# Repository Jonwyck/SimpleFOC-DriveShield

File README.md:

> Fork additions: [v1.8 pinout and jumper guide](Design/DriveShield_pinout.org), [HTML guide](Design/DriveShield_pinout.html), and [initial KiCad 10 import](KiCad/README.org). The KiCad copy needs ERC/DRC and library/linkage cleanup before fabrication. Original EasyEDA design files remain unchanged.

# *Simple**FOC*** ***Drive**Shield* *v1.8*

This is an open-source low-cost BLDC driver boards in the form of a Arduino shield. It is a part of the *Simple**FOC*** project. The board is the big brother of the *Simple**FOC**Shield* and is designed to drive motors with higher current requirements, up to 40Amps. The board is created with the same philosophy as the *Simple**FOC**Shield* - to be simple to use, low-cost, and open-source and fully compatible with the *Simple**FOC***library. 

Additionally the aim of the board is to serve as a template project for the community to build their own motor drivers. 
- The board is relatively simple and can be easily modified to fit different requirements.
- The board is designed in EasyEDA and all the fabrication files are available for download

📢 NEW: This board is now available in our collaboration with **Makerfabs**: [See more on makerfabs.com](https://www.makerfabs.com/simplefoc-driveshield.html)

### Components
- **DRV8320H** gate driver - [datahseet](https://www.ti.com/lit/ds/symlink/drv8320.pdf?ts=178671431434)
   - Hardware configuration 
   - 3PWM 
   - Protections: undervoltage lockout, charge pump fault, MOSFET overcurrent, MOSFET short circuit, gate driver fault and overtemperature
- **BSZ0904NSI** mosfets
   - Standard 3mm x 3mm footprint (can be easily exchanged)
   - Max current 75A 
   - Max voltage 30V
- **INA240A1**: - [datasheet](https://www.ti.com/lit/ds/symlink/ina240.pdf?ts=1786684614540)
   - Inline current sensor
   - Gain 20V/V
   - Shunt resistor: 2mΩ (parallel of 4mΩ)
   - 40A measurement range bidirectional (at 3.3V)
- **LM7808**:
   - 8V LDO voltage regulator to VIN 

### Features
- **Boards absolute max ratings** 
   - Max current: 20A continuous (peak 30A - measured) 
   - Max input voltage: 30V
- **Stackable**: running 2 motors in the same time
- **Encoder/Hall sensors interface**: Integrated 3.3kΩ pullups (configurable)
- **I2C interface**: Integrated 4.7kΩ pullups (configurable)
- **Configurable pinout**: Hardware configuration - soldering connections
- **stemma QT connector**: for easy connection of sensors and peripherals
- **JST SPI connector**: for easy connection of SPI devices (only one SPI device can be connected at a time)
- **Arduino headers**: Arduino UNO, Arduino MEGA, STM32 Nucleo boards...
- **Open Source**: 
   - Fully designed in **EasyEDA**: [EasyEDA project](https://oshwlab.com/the.skuric/SimpleFOC-Drive)
   - Fully available fabrication files - [how to make it yourself](https://docs.simplefoc.com/arduino_simplefoc_shield_fabrication)
- **Low-cost**: Estimated price of 25€ - See more in [our shop](https://simplefoc.com/shop)

## Shield version comparison

Feature | <span class="simple">Simple<span class="foc">FOC</span>Shield</span> v1.x | <span class="simple">Simple<span class="foc">FOC</span>Shield</span> v2.x | <span class="simple">Simple<span class="foc">FOC</span>Shield</span> v3.x | <span class="simple">Simple<span class="foc">FOC</span> <b>Drive</b>Shield</span> v1.x
|-|-|-|-|-|
|||||
**PWM Driver** | [L6234](https://www.st.com/resource/en/datasheet/l6234.pdf) | [L6234](https://www.st.com/resource/en/datasheet/l6234.pdf) | [DRV8313](https://www.ti.com/lit/ds/symlink/drv8313.pdf?ts=1719165774986&ref_url=https%253A%252F%252Fwww.google.com%252F)| gate driver: [DRV8320H](https://www.ti.com/lit/ds/symlink/drv8320.pdf) <br> mosfets: [BSZ0904NSI](https://www.infineon.com/dgdl/Infineon-BSZ0904NSI-DataSheet-v02_04-EN.pdf?fileId=db3a30432f29829e012f2a1ec7d90032)
**Current Sense** | ❌ | [INA240](https://www.ti.com/lit/ds/symlink/ina240.pdf?ts=1719180172738) | [ACS712 (5A)](https://www.allegromicro.com/en/products/sense/current-sensor-ics/zero-to-fifty-amp-integrated-conductor-sensor-ics/acs712) | [INA240](https://www.ti.com/lit/ds/symlink/ina240.pdf?ts=1719180172738)
**Current measurement range** | ❌ | (configurable) ±3.3/5Amps | ±5Amps | ±40Amps
**Onboard LDO** | ❌ | LM7808 | LM7808 | LM7808 (v1.8+)
**Stackable** | ✔️ | ✔️ | ✔️ | ✔️
**Max current** | 2Amps (5Amp peak) | 2Amps (5Amp peak) | 2Amps (3Amp peak) | 20Amps (40Amp peak)
**Max voltage** | 24V | 35V | 35V | 30V 
**Protections** | Overtemperature | Overtemperature | Overtemperature, Overcurrent | undervoltage lockout, charge pump fault, MOSFET overcurrent, MOSFET short circuit, gate driver fault, overtemperature
**Footprint** | 68mm x 53 mm | 68mm x 53 mm | 56mm x 53mm | 56mm x 53mm
**Design tool** | Altium Designer 2019 | Altium Designer 2019 | EasyEDA | EasyEDA 

## Board evolution timeline

To check the release timeline, click [here](https://github.com/simplefoc/SimpleFOC-driveShield/releases) 

Version  | release | Release date | Comment
----- | ----- | ---- | ----
*Simple**FOC** **Drive**Shield* v1.0 | v0.1 | 05/24 | - Test version <br> - **DRV8300** gate driver <br> - **SE3082G** dual mosfets <br> - ACS712 (range +-30Amps) <br> - 20V max voltage 
*Simple**FOC** **Drive**Shield* v1.0 | v1.0 | 06/24 | - Transition to **DRV8320H** gate driver <br>  - 30V max voltage
*Simple**FOC** **Drive**Shield* v1.1 | v1.1 | 07/24 | - Transition to 3x3mm **BSZ09x** mosfets instead of **SE3082G** <br> - 30V max voltage
*Simple**FOC** **Drive**Shield* v1.2 | [v1.2](https://github.com/simplefoc/SimpleFOC-DriveShield/releases/tag/v1.2) | 08/24 | Initial release <br>- Transition to **4 layer** PCB <br> - Enabling stacking (soldering pads) <br> - Configurable pullups (I2C and encoder) 
*Simple**FOC** **Drive**Shield* v1.7 | v1.7 | 02/26 | - stemma QT connector<br>-SPI connector<br>- INA240 current sensing <br>- Power supply measurement
*Simple**FOC** **Drive**Shield* v1.8 | v1.8 | 06/26 | - added LDO to power the board from VIN (8V) 

## Size comparison with SimpleFOCShield v3

## Temperature characteristics study

This board can measure the phase currents up to 30Amps, so it is intended to be used in applications that require current draw up to around 20Amps continuous. For higher currents especially in the range of 15-30Amps the board can get quite hot. Depending on the copper thickness of the PCB chosen when ordering the board the temperature can vary, as well as the cooling conditions. The board can be fitted with a heatsink to improve the thermal performance.

So I've wanted to quantify the temperature characteristics of the board when a continuous current is applied to the motor. The measurements were done with a relatively constant ambient temperature of around 25°C. The board was powered with 24V. The motor was run at very low speed (0.1rad/s) in the open loop and the current (q component) was set to 10, 15 and 20 amps for prolonged periods of time. I've measured the temperature on the top of the board on the DRV8320H gate driver and the BSZ0904NSI mosfets. I've used the PICOLOG TC-08 thermocouple data logger to do the measuring.

Two copper thicknesses were tested
1. Standard 4-layer: 
    - **1oz** (35um) copper thickness on top and bottom layers, 
    - **0.5oz** (17.5um) copper thickness on inner layers

2. Thick 4-layer: 
    - **2oz** (70um) copper thickness on top and bottom layers, 
    - **0.5oz** (35um) copper thickness on inner layers

### Experiment results
Here is the table of the results

Current [A] | Standard 4-layer MOSFETS | Thick 4-layer  MOSFETS | Standard 4-layer DRV8320 |  Thick 4-layer DRV8320 
--- | --- | ---| --- | ---
10 | 57°C| 53°C | 50°C  | 52°C
15 | 78°C | 68°C| 62°C  | 62°C
20 | 125°C  | 100°C | 82°C | 82°C

So the results seem to suggest that, as the **BSZ0904NSI** mosfets are rated for temperatures up to 150°C and the **DRV8320H** gate driver up to 125°C, the board can be used up to 20Amps without additional cooling. 

**However, I would definitely recommend using a heatsink or a thicker copper PCB (2oz top and bottom layers) for currents above 15Amps continuous.**

<details>
<summary>Measured temperatures during the experiment</summary>

</details>

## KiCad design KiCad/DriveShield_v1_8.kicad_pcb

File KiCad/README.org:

#+TITLE: DriveShield v1.8 initial native KiCad import
#+DATE: 2026-09-27

Open DriveShield_v1_8.kicad_pro in KiCad 10.0.1 or later.

This is an inspection/migration copy of the unchanged upstream EasyEDA design, not a fabrication release. Read ../Design/DriveShield_pinout.org (or its HTML export) before using it.

* Validation
- Schematic loaded in the native editor and exported to PDF and XML netlist.
- PCB imported with the native EasyEDA Standard importer; importer reports zero errors/warnings.
- All 301 source pad instances, including standalone pads, retain their pad number and net name in the imported PCB (pad-net-audit.json).
- ERC: 439 findings. Schematic references, pin electrical types, library assignments and dangling source labels need work.
- PCB DRC completed outside the sandbox: 1322 findings, including 862 errors and 460 warnings; zero unconnected items. Zero unconnected items does not establish schematic/PCB parity.
- Footprints and schematic symbols have not been reconciled for safe Update PCB from Schematic.
- Original circuit and original source files were not modified.

* Reproduction
- Source commit: 22b4c5506e67aa473017a09c13aa4fd4a453504b.
- PCB: kicad-cli pcb import ../EasyEDA/PCB_pcb_drive_2026-08-14.json --output DriveShield_v1_8.kicad_pcb.
- Schematic: in standalone Schematic Editor, File > Import > Non-KiCad Schematic; select ../EasyEDA/SCH_SimpleFOC-Drive_2026-08-14.json; save as DriveShield_v1_8.kicad_sch in this directory.
- Import creates embedded schematic symbols; shared symbol/footprint libraries still require migration work.

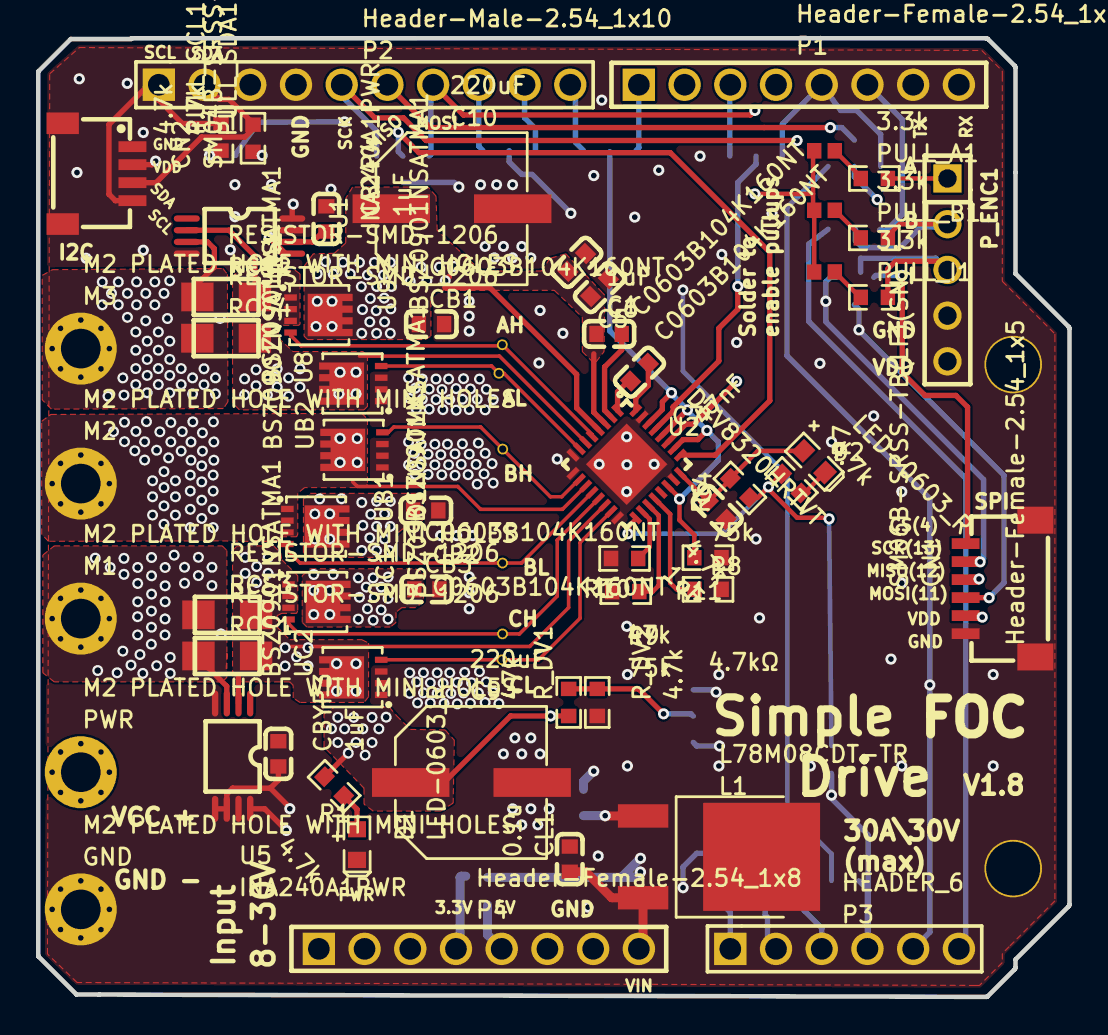
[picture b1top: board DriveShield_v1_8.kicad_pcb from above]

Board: 4 copper layers, 57.3 x 53.3 mm, 112 parts (0 on the bottom side), 63 nets.

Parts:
C1, C5: C0603B104K160NT; C0603
C4, C6: 1uF; C0603
C7: 47nF; C0603
C9, C10: 220uF; CAP-SMD_BD8.0-L8.3-W8.3-LS9.5-FD
CB1, CB2, CB3: C0603B104K160NT; C0603
CBYP3, CBYP4: 1uF; C0603
CL1: 0.1u; C0603
CN1: SM06B-SRSS-TB(LF)(SN); CONN-SMD_SM06B-SRSS-TB-LF-SN
CN2: SM04B-SRSS-TB(LF)(SN)(P); CONN-SMD_4P-P1.00_SM04B-SRSS-TB-LF-SN
D1, D2: LED-0603_R; LED0603_RED
GND: M2 PLATED HOLE WITH MINI HOLES
L1: L78M08CDT-TR; TO-252-2_L6.6-W6.1-P4.57-LS9.9-TL-CW
M1, M2, M3: M2 PLATED HOLE WITH MINI HOLES
P1, P4: Header-Female-2.54_1x8; HDR-TH_8P-P2.54-V-F-1
P2: Header-Male-2.54_1x10; HDR-TH_10P-P2.54-V-M-1
P3: HEADER_6; HDR-M-2.54_1X6
PULL_A1: 3.3k; R0603
PULL_B1: 3.3k; R0603
PULL_I1: 3.3k; R0603
PULL_SCL1: 4.7k; R0603
PULL_SDA1: 4.7k; R0603
PWR: M2 PLATED HOLE WITH MINI HOLES
P_ENC1: Header-Female-2.54_1x5; HDR-TH_5P-P2.54-V-F
Pad_gge24965: Pad_gge24965
Pad_gge25001: Pad_gge25001
Pad_gge25037: Pad_gge25037
Pad_gge25067: Pad_gge25067
Pad_gge25094: Pad_gge25094
Pad_gge25115: Pad_gge25115
Pad_gge39070: Pad_gge39070
Pad_gge39073: Pad_gge39073
Pad_gge39076: Pad_gge39076
Pad_gge49879: Pad_gge49879
Pad_gge49948: Pad_gge49948
Pad_gge49993: Pad_gge49993
Pad_gge50014: Pad_gge50014
Pad_gge50035: Pad_gge50035
Pad_gge50056: Pad_gge50056
Pad_gge56675: Pad_gge56675
Pad_gge56678: Pad_gge56678
Pad_gge56681: Pad_gge56681
Pad_gge56738: Pad_gge56738
Pad_gge56741: Pad_gge56741
Pad_gge56744: Pad_gge56744
Pad_gge57389: Pad_gge57389
Pad_gge57392: Pad_gge57392
Pad_gge57395: Pad_gge57395
Pad_gge57743: Pad_gge57743
Pad_gge57746: Pad_gge57746
Pad_gge57749: Pad_gge57749
Pad_gge58091: Pad_gge58091
Pad_gge58094: Pad_gge58094
Pad_gge58097: Pad_gge58097
Pad_gge58325: Pad_gge58325
Pad_gge58328: Pad_gge58328
Pad_gge58331: Pad_gge58331
Pad_gge58361: Pad_gge58361
Pad_gge59666: Pad_gge59666
Pad_gge59669: Pad_gge59669
Pad_gge60145: Pad_gge60145
Pad_gge60148: Pad_gge60148
Pad_gge60151: Pad_gge60151
Pad_gge60328: Pad_gge60328
Pad_gge60331: Pad_gge60331
Pad_gge60334: Pad_gge60334
Pad_gge60337: Pad_gge60337
Pad_gge60853: Pad_gge60853
Pad_gge60856: Pad_gge60856
Pad_gge60859: Pad_gge60859
Pad_gge60862: Pad_gge60862
Pad_gge75108: Pad_gge75108
Pad_gge75111: Pad_gge75111
Pad_gge75114: Pad_gge75114
Pad_gge85978: Pad_gge85978
Pad_gge85981: Pad_gge85981
Pad_gge85984: Pad_gge85984
Pad_gge90416: Pad_gge90416
Pad_gge90419: Pad_gge90419
Pad_rep9: Pad_rep9
Pad_rep11: Pad_rep11
R1, R6, R7: 4.7k; R0603
R8, R9: 75k; R0603
R10: 47k; R0603
R11: 4.7kΩ; R0603
RCS1, RCS2, RCS3, RCS4: RESISTOR-SMD-1206
R_DV1: 47k; R0603
R_DV2: 4.7k; R0603
U1, U5: INA240A1PWR; TSSOP-8_L4.4-W3.0-P0.65-LS6.4-BL
U2: DRV8320HRTVT; WQFN-32_L5.0-W5.0-P0.50-TL-EP
U8, U9: BSZ0901NSATMA1; DFN-8_L3.3-W3.3-P0.65-BL-2
UB1, UB2: BSZ0901NSATMA1; DFN-8_L3.3-W3.3-P0.65-BL-2
UC1, UC2: BSZ0901NSATMA1; DFN-8_L3.3-W3.3-P0.65-BL-2

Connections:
0.1_VCC: Pad_gge85981.0.1_VCC, R_DV1.2, R_DV2.1
3.3V: P4.4, Pad_gge39073.2
+5V: P4.5, Pad_gge39076.2
C1_OUT: Pad_gge56741.2, U1.8
C2_OUT: Pad_gge56678.2, U5.8
C6_2: C6.2, U2.2
C7_1: C7.1, U2.32
C7_2: C7.2, U2.1
D1_1: D1.1, R1.1
D2_2: D2.2, R7.2
DVDD: C4.2, D2.1, R6.2, U2.24
ENABLE: Pad_gge57392.2, R11.2, U2.22, U2.26, U2.28, U2.30
ENC_A: PULL_A1.2, P_ENC1.1, Pad_gge60331.2
ENC_A_SP: PULL_A1.1, Pad_gge25067.1
ENC_B: PULL_B1.2, P_ENC1.2, Pad_gge60148.2
ENC_B_SP: PULL_B1.1, Pad_gge25094.1
ENC_I: PULL_I1.2, P_ENC1.3, Pad_gge60856.2
ENC_I_SP: PULL_I1.1, Pad_gge25115.2
GHA: Pad_gge49879.5, U2.5, U9.4
GHB: Pad_gge50014.5, U2.12, UB1.4
GHC: Pad_gge50035.5, U2.13, UC1.4
GLA: Pad_gge49948.5, U2.7, U8.4
GLB: Pad_gge49993.5, U2.10, UB2.4
GLC: Pad_gge50056.5, U2.15, UC2.4
GND: C1.1, C4.1, C5.1, C9.2, C10.2, CB1.2, CB2.1, CB3.2, CBYP3.1, CBYP4.1, CL1.2, CN1.1, CN1.7, CN1.8, CN2.1, CN2.5, CN2.6, D1.2, GND.1, L1.2, P2.4, P4.6, P4.7, P_ENC1.4, R8.2, R9.2, R10.2, R11.1, R_DV2.2, U1.4, U1.7, U2.8, U2.9, U2.16, U2.23, U2.31, U2.33, U5.4, U5.7, U8.1, U8.2, U8.3, UB2.1, UB2.2, UB2.3, UC2.1, UC2.2, UC2.3
IDRIVE: R9.1, U2.19
INHA: Pad_gge58328.2, U2.25
INHB: Pad_gge58094.2, U2.27
INHC: Pad_gge57746.2, U2.29
L1_1: L1.1, Pad_gge90419.2
MODE: R10.1, U2.18
NFLT: Pad_gge59669.2, R6.1, R7.1, U2.17
PIN2: P1.6, Pad_gge60145.2
PIN3: P1.5, Pad_gge57743.2, Pad_gge60334.2
PIN4: CN1.6, P1.4, Pad_gge60859.2
PIN5: P1.3, Pad_gge57749.2
PIN6: P1.2, Pad_gge58361.2
PIN7: P1.1, Pad_gge57389.2
PIN8: P2.10, Pad_gge57395.2
PIN9: P2.9, Pad_gge58091.2
PIN10: P2.8, Pad_gge58097.2
PIN11: CN1.3, P2.7, Pad_gge58325.2, Pad_gge60862.2
PIN12: CN1.4, P2.6, Pad_gge60337.2
PIN13: CN1.5, P2.5, Pad_gge58331.2, Pad_gge60853.2
PINA0: P3.1, Pad_gge56675.2
PINA1: P3.2, Pad_gge56681.2
PINA2: P3.3, Pad_gge56738.2
PINA3: P3.4, Pad_gge56744.2, Pad_gge59666.2, Pad_gge85978.2
PINA4: P3.5, Pad_gge60328.2, Pad_gge85984.2
PINA5: P3.6, Pad_gge60151.2
SCL: CN2.4, P2.1, PULL_SCL1.2
SCL_SP: PULL_SCL1.1, Pad_gge75108.2
SDA: CN2.3, P2.2, PULL_SDA1.2
SDA_SP: PULL_SDA1.1, Pad_gge75114.2
SHA: RCS2.1, RCS4.1, U1.2, U2.6, U8.5, U9.1, U9.2, U9.3
SHA_CS: M3.1, RCS2.2, RCS4.2, U1.3
SHB: M2.1, U2.11, UB1.1, UB1.2, UB1.3, UB2.5
SHC: RCS1.1, RCS3.1, U2.14, U5.2, UC1.1, UC1.2, UC1.3, UC2.5
SHC_CS: M1.1, RCS1.2, RCS3.2, U5.3
VCC: C1.2, C5.2, C6.1, C9.1, C10.1, CB1.1, CB2.2, CB3.1, PWR.1, Pad_gge90416.VCC, R1.2, R_DV1.1, U2.3, U2.4, U9.5, UB1.5, UC1.5
VDD: CBYP3.2, CBYP4.2, CN1.2, CN2.2, P_ENC1.5, Pad_gge24965.2, Pad_gge25001.2, Pad_gge25037.2, Pad_gge39070.2, Pad_gge75111.2, U1.5, U1.6, U5.5, U5.6
VDS: R8.1, U2.20
VIN: CL1.1, L1.3, P4.8

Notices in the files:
README.md:
License: MIT
